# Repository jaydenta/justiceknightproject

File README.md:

# justiceknightproject
kicad and step files for new project

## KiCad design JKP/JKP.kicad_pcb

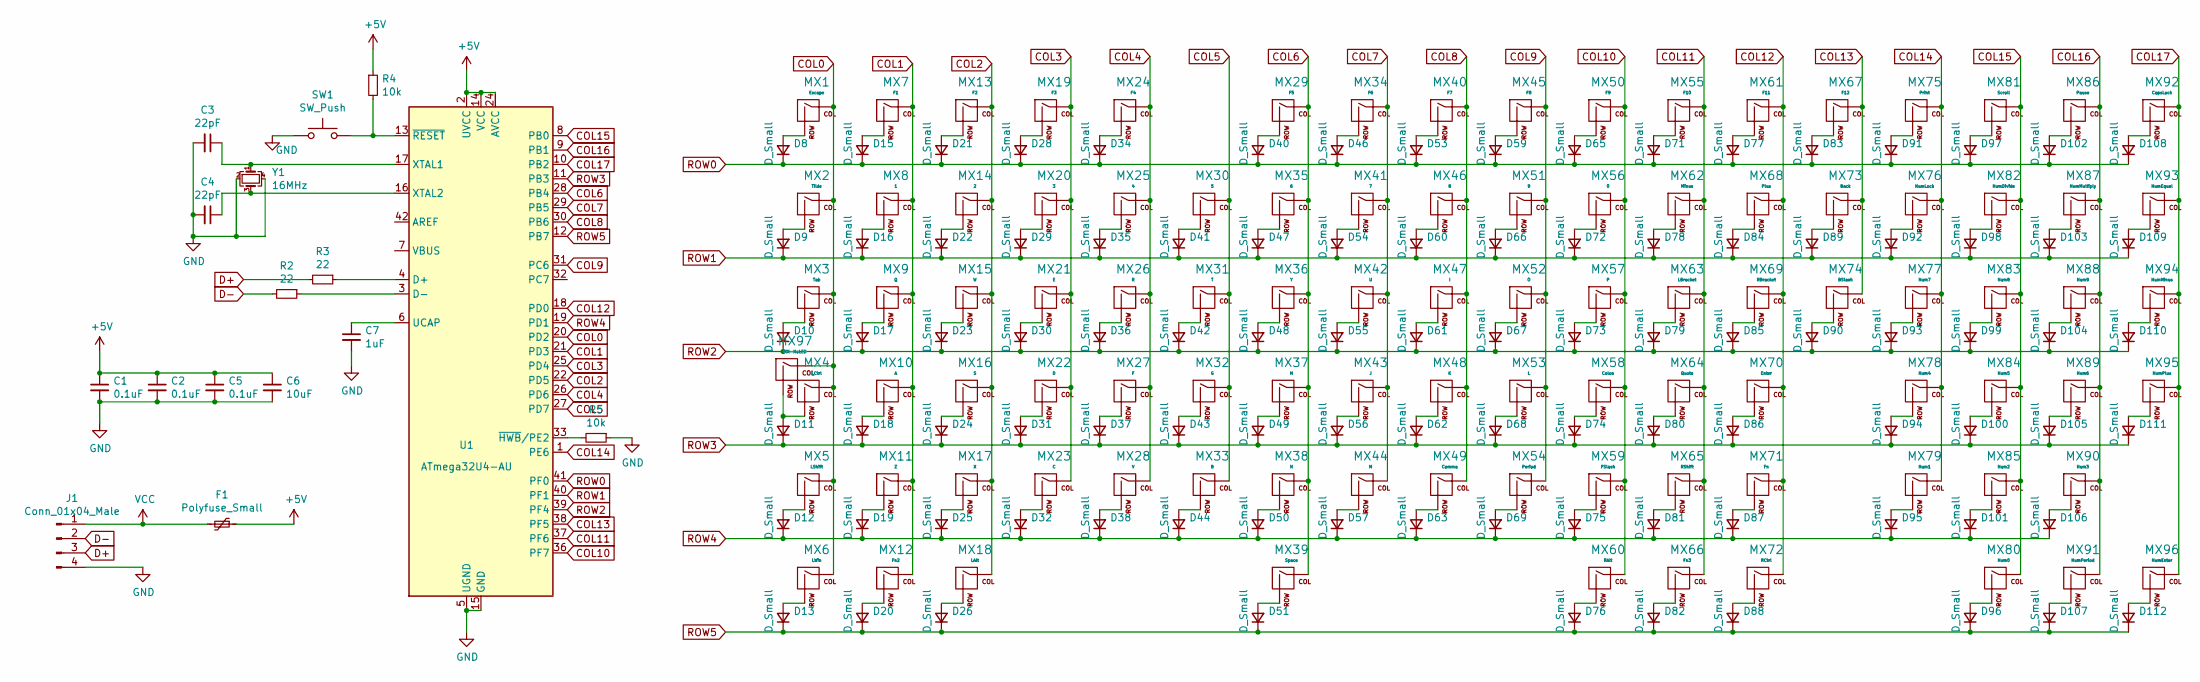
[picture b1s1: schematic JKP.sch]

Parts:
C1, C2, C5: 0.1uF; C_0805_2012Metric
C3, C4: 22pF; C_0805_2012Metric
C6: 10uF; C_0805_2012Metric
C7: 1uF; C_0805_2012Metric
D8, D9, D10, D11, D12, D13, D15, D16, D17, D18, D19, D20, D21, D22, D23, D24, D25, D26, D28, D29, D30, D31, D32, D34, D35, D36, D37, D38, D40, D41, D42, D43, D44, D46, D47, D48, D49, D50, D51, D53, D54, D55, D56, D57, D59, D60, D61, D62, D63, D65, D66, D67, D68, D69, D71, D72, D73, D74, D75, D76, D77, D78, D79, D80, D81, D82, D83, D84, D85, D86, D87, D88, D89, D90, D91, D92, D93, D94, D95, D96, D97, D98, D99, D100, D101, D102, D103, D104, D105, D106, D107, D108, D109, D110, D111, D112: D_Small; D_SOD-123
F1: Polyfuse_Small; Fuse_1206_3216Metric
J1: Conn_01x04_Male; JST_SH_SM04B-SRSS-TB_1x04-1MP_P1.00mm_Horizontal
MX1: Escape; MX-1U-NoLED
MX2: Tilde; MX-1U-NoLED
MX3: Tab; MX-1.5U-NoLED
MX4: LCtrl; MX-1.25U-NoLED
MX5: LShift; MX-2.25U-NoLED
MX6: LWin; MX-1.5U-NoLED
MX7: F1; MX-1U-NoLED
MX8: 1; MX-1U-NoLED
MX9: Q; MX-1U-NoLED
MX10: A; MX-1U-NoLED
MX11: Z; MX-1U-NoLED
MX12: Fn2; MX-1U-NoLED
MX13: F2; MX-1U-NoLED
MX14: 2; MX-1U-NoLED
MX15: W; MX-1U-NoLED
MX16: S; MX-1U-NoLED
MX17: X; MX-1U-NoLED
MX18: LAlt; MX-1.5U-NoLED
MX19: F3; MX-1U-NoLED
MX20: 3; MX-1U-NoLED
MX21: E; MX-1U-NoLED
MX22: D; MX-1U-NoLED
MX23: C; MX-1U-NoLED
MX24: F4; MX-1U-NoLED
MX25: 4; MX-1U-NoLED
MX26: R; MX-1U-NoLED
MX27: F; MX-1U-NoLED
MX28: V; MX-1U-NoLED
MX29: F5; MX-1U-NoLED
MX30: 5; MX-1U-NoLED
MX31: T; MX-1U-NoLED
MX32: G; MX-1U-NoLED
MX33: B; MX-1U-NoLED
MX34: F6; MX-1U-NoLED
MX35: 6; MX-1U-NoLED
MX36: Y; MX-1U-NoLED
MX37: H; MX-1U-NoLED
MX38: N; MX-1U-NoLED
MX39: Space; MX-7U-ReversedStabilizers-NoLED
MX40: F7; MX-1U-NoLED
MX41: 7; MX-1U-NoLED
MX42: U; MX-1U-NoLED
MX43: J; MX-1U-NoLED
MX44: M; MX-1U-NoLED
MX45: F8; MX-1U-NoLED
MX46: 8; MX-1U-NoLED
MX47: I; MX-1U-NoLED
MX48: K; MX-1U-NoLED
MX49: Comma; MX-1U-NoLED
MX50: F9; MX-1U-NoLED
MX51: 9; MX-1U-NoLED
MX52: O; MX-1U-NoLED
MX53: L; MX-1U-NoLED
MX54: Period; MX-1U-NoLED
MX55: F10; MX-1U-NoLED
MX56: 0; MX-1U-NoLED
MX57: P; MX-1U-NoLED
MX58: Colon; MX-1U-NoLED
MX59: FSlash; MX-1U-NoLED
MX60: RAlt; MX-1.5U-NoLED
MX61: F11; MX-1U-NoLED
MX62: Minus; MX-1U-NoLED
MX63: LBracket; MX-1U-NoLED
MX64: Quote; MX-1U-NoLED
MX65: RShift; MX-1.75U-NoLED
MX66: Fn3; MX-1U-NoLED
MX67: F12; MX-1U-NoLED
MX68: Plus; MX-1U-NoLED
MX69: RBracket; MX-1U-NoLED
MX70: Enter; MX-2.25U-NoLED
MX71: Fn; MX-1U-NoLED
MX72: RCtrl; MX-1.5U-NoLED
MX73: Back; MX-2U-NoLED
MX74: BSlash; MX-1.5U-NoLED
MX75: Print; MX-1U-NoLED
MX76: NumLock; MX-1U-NoLED
MX77: Num7; MX-1U-NoLED
MX78: Num4; MX-1U-NoLED
MX79: Num1; MX-1U-NoLED
MX80: Num0; MX-2U-ReversedStabilizers-NoLED
MX81: Scroll; MX-1U-NoLED
MX82: NumDivide; MX-1U-NoLED
MX83: Num8; MX-1U-NoLED
MX84: Num5; MX-1U-NoLED
MX85: Num2; MX-1U-NoLED
MX86: Pause; MX-1U-NoLED
MX87: NumMultiply; MX-1U-NoLED
MX88: Num9; MX-1U-NoLED
MX89: Num6; MX-1U-NoLED
MX90: Num3; MX-1U-NoLED
MX91: NumPeriod; MX-1U-NoLED
MX92: CapsLock; MX-1U-NoLED
MX93: NumEqual; MX-1U-NoLED
MX94: NumMinus; MX-1U-NoLED
MX95: NumPlus; MX-1U-NoLED
MX96: NumEnter; MX-2U-ReversedStabilizers-NoLED
MX97: MX-NoLED; MX-1.5U-NoLED
R2, R3: 22; R_0805_2012Metric
R4, R5: 10k; R_0805_2012Metric
SW1: SW_Push; SKQG-1155865
U1: ATmega32U4-AU; TQFP-44_10x10mm_P0.8mm
Y1: 16MHz; Crystal_SMD_3225-4Pin_3.2x2.5mm

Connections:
+5V: C1.1, C2.1, C5.1, C6.1, F1.1, R4.1, U1.2 (UVCC), U1.14 (VCC), U1.24 (AVCC), U1.34 (VCC), U1.44 (AVCC)
COL0: MX1.1 (COL), MX2.1 (COL), MX3.1 (COL), MX4.1 (COL), MX5.1 (COL), MX6.1 (COL), MX97.1 (COL), U1.20 (PD2)
COL1: MX7.1 (COL), MX8.1 (COL), MX9.1 (COL), MX10.1 (COL), MX11.1 (COL), MX12.1 (COL), U1.21 (PD3)
COL2: MX13.1 (COL), MX14.1 (COL), MX15.1 (COL), MX16.1 (COL), MX17.1 (COL), MX18.1 (COL), U1.22 (PD5)
COL3: MX19.1 (COL), MX20.1 (COL), MX21.1 (COL), MX22.1 (COL), MX23.1 (COL), U1.25 (PD4)
COL4: MX24.1 (COL), MX25.1 (COL), MX26.1 (COL), MX27.1 (COL), MX28.1 (COL), U1.26 (PD6)
COL5: MX30.1 (COL), MX31.1 (COL), MX32.1 (COL), MX33.1 (COL), U1.27 (PD7)
COL6: MX29.1 (COL), MX35.1 (COL), MX36.1 (COL), MX37.1 (COL), MX38.1 (COL), MX39.1 (COL), U1.28 (PB4)
COL7: MX34.1 (COL), MX41.1 (COL), MX42.1 (COL), MX43.1 (COL), MX44.1 (COL), U1.29 (PB5)
COL8: MX40.1 (COL), MX46.1 (COL), MX47.1 (COL), MX48.1 (COL), MX49.1 (COL), U1.30 (PB6)
COL9: MX45.1 (COL), MX51.1 (COL), MX52.1 (COL), MX53.1 (COL), MX54.1 (COL), U1.31 (PC6)
COL10: MX50.1 (COL), MX56.1 (COL), MX57.1 (COL), MX58.1 (COL), MX59.1 (COL), MX60.1 (COL), U1.36 (PF7)
COL11: MX55.1 (COL), MX62.1 (COL), MX63.1 (COL), MX64.1 (COL), MX65.1 (COL), MX66.1 (COL), U1.37 (PF6)
COL12: MX61.1 (COL), MX68.1 (COL), MX69.1 (COL), MX70.1 (COL), MX71.1 (COL), MX72.1 (COL), U1.18 (PD0)
COL13: MX67.1 (COL), MX73.1 (COL), MX74.1 (COL), U1.38 (PF5)
COL14: MX75.1 (COL), MX76.1 (COL), MX77.1 (COL), MX78.1 (COL), MX79.1 (COL), U1.1 (PE6)
COL15: MX80.1 (COL), MX81.1 (COL), MX82.1 (COL), MX83.1 (COL), MX84.1 (COL), MX85.1 (COL), U1.8 (PB0)
COL16: MX86.1 (COL), MX87.1 (COL), MX88.1 (COL), MX89.1 (COL), MX90.1 (COL), MX91.1 (COL), U1.9 (PB1)
COL17: MX92.1 (COL), MX93.1 (COL), MX94.1 (COL), MX95.1 (COL), MX96.1 (COL), U1.10 (PB2)
D+: J1.3, R3.2
D-: J1.2, R2.2
GND: C1.2, C2.2, C3.2, C4.2, C5.2, C6.2, C7.2, J1.4, R5.1, SW1.1, U1.5 (UGND), U1.15 (GND), U1.23 (GND), U1.35 (GND), U1.43 (GND), Y1.2, Y1.4
unnamed: C3.1, U1.17 (XTAL1), Y1.1
unnamed: C4.1, U1.16 (XTAL2), Y1.3
unnamed: C7.1, U1.6 (UCAP)
unnamed: D8.2 (A), MX1.2 (ROW)
unnamed: D9.2 (A), MX2.2 (ROW)
unnamed: D10.2 (A), MX3.2 (ROW)
unnamed: D11.2 (A), MX4.2 (ROW), MX97.2 (ROW)
unnamed: D12.2 (A), MX5.2 (ROW)
unnamed: D13.2 (A), MX6.2 (ROW)
unnamed: D15.2 (A), MX7.2 (ROW)
unnamed: D16.2 (A), MX8.2 (ROW)
unnamed: D17.2 (A), MX9.2 (ROW)
unnamed: D18.2 (A), MX10.2 (ROW)
unnamed: D19.2 (A), MX11.2 (ROW)
unnamed: D20.2 (A), MX12.2 (ROW)
unnamed: D21.2 (A), MX13.2 (ROW)
unnamed: D22.2 (A), MX14.2 (ROW)
unnamed: D23.2 (A), MX15.2 (ROW)
unnamed: D24.2 (A), MX16.2 (ROW)
unnamed: D25.2 (A), MX17.2 (ROW)
unnamed: D26.2 (A), MX18.2 (ROW)
unnamed: D28.2 (A), MX19.2 (ROW)
unnamed: D29.2 (A), MX20.2 (ROW)
unnamed: D30.2 (A), MX21.2 (ROW)
unnamed: D31.2 (A), MX22.2 (ROW)
unnamed: D32.2 (A), MX23.2 (ROW)
unnamed: D34.2 (A), MX24.2 (ROW)
unnamed: D35.2 (A), MX25.2 (ROW)
unnamed: D36.2 (A), MX26.2 (ROW)
unnamed: D37.2 (A), MX27.2 (ROW)
unnamed: D38.2 (A), MX28.2 (ROW)
unnamed: D40.2 (A), MX29.2 (ROW)
unnamed: D41.2 (A), MX30.2 (ROW)
unnamed: D42.2 (A), MX31.2 (ROW)
unnamed: D43.2 (A), MX32.2 (ROW)
unnamed: D44.2 (A), MX33.2 (ROW)
unnamed: D46.2 (A), MX34.2 (ROW)
unnamed: D47.2 (A), MX35.2 (ROW)
unnamed: D48.2 (A), MX36.2 (ROW)
unnamed: D49.2 (A), MX37.2 (ROW)
unnamed: D50.2 (A), MX38.2 (ROW)
unnamed: D51.2 (A), MX39.2 (ROW)
unnamed: D53.2 (A), MX40.2 (ROW)
unnamed: D54.2 (A), MX41.2 (ROW)
unnamed: D55.2 (A), MX42.2 (ROW)
unnamed: D56.2 (A), MX43.2 (ROW)
unnamed: D57.2 (A), MX44.2 (ROW)
unnamed: D59.2 (A), MX45.2 (ROW)
unnamed: D60.2 (A), MX46.2 (ROW)
unnamed: D61.2 (A), MX47.2 (ROW)
unnamed: D62.2 (A), MX48.2 (ROW)
unnamed: D63.2 (A), MX49.2 (ROW)
unnamed: D65.2 (A), MX50.2 (ROW)
unnamed: D66.2 (A), MX51.2 (ROW)
unnamed: D67.2 (A), MX52.2 (ROW)
unnamed: D68.2 (A), MX53.2 (ROW)
unnamed: D69.2 (A), MX54.2 (ROW)
unnamed: D71.2 (A), MX55.2 (ROW)
unnamed: D72.2 (A), MX56.2 (ROW)
unnamed: D73.2 (A), MX57.2 (ROW)
unnamed: D74.2 (A), MX58.2 (ROW)
unnamed: D75.2 (A), MX59.2 (ROW)
unnamed: D76.2 (A), MX60.2 (ROW)
unnamed: D77.2 (A), MX61.2 (ROW)
unnamed: D78.2 (A), MX62.2 (ROW)
unnamed: D79.2 (A), MX63.2 (ROW)
unnamed: D80.2 (A), MX64.2 (ROW)
unnamed: D81.2 (A), MX65.2 (ROW)
unnamed: D82.2 (A), MX66.2 (ROW)
unnamed: D83.2 (A), MX67.2 (ROW)
unnamed: D84.2 (A), MX68.2 (ROW)
unnamed: D85.2 (A), MX69.2 (ROW)
unnamed: D86.2 (A), MX70.2 (ROW)
unnamed: D87.2 (A), MX71.2 (ROW)
unnamed: D88.2 (A), MX72.2 (ROW)
unnamed: D89.2 (A), MX73.2 (ROW)
unnamed: D90.2 (A), MX74.2 (ROW)
unnamed: D91.2 (A), MX75.2 (ROW)
unnamed: D92.2 (A), MX76.2 (ROW)
unnamed: D93.2 (A), MX77.2 (ROW)
unnamed: D94.2 (A), MX78.2 (ROW)
unnamed: D95.2 (A), MX79.2 (ROW)
unnamed: D96.2 (A), MX80.2 (ROW)
unnamed: D97.2 (A), MX81.2 (ROW)
unnamed: D98.2 (A), MX82.2 (ROW)
unnamed: D99.2 (A), MX83.2 (ROW)
unnamed: D100.2 (A), MX84.2 (ROW)
unnamed: D101.2 (A), MX85.2 (ROW)
unnamed: D102.2 (A), MX86.2 (ROW)
unnamed: D103.2 (A), MX87.2 (ROW)
unnamed: D104.2 (A), MX88.2 (ROW)
unnamed: D105.2 (A), MX89.2 (ROW)
unnamed: D106.2 (A), MX90.2 (ROW)
unnamed: D107.2 (A), MX91.2 (ROW)
unnamed: D108.2 (A), MX92.2 (ROW)
unnamed: D109.2 (A), MX93.2 (ROW)
unnamed: D110.2 (A), MX94.2 (ROW)
unnamed: D111.2 (A), MX95.2 (ROW)
unnamed: D112.2 (A), MX96.2 (ROW)
unnamed: R2.1, U1.3 (D-)
unnamed: R3.1, U1.4 (D+)
unnamed: R4.2, SW1.2, U1.13 (~RESET)
unnamed: R5.2, U1.33 (~HWB~/PE2)
ROW0: D8.1 (K), D15.1 (K), D21.1 (K), D28.1 (K), D34.1 (K), D40.1 (K), D46.1 (K), D53.1 (K), D59.1 (K), D65.1 (K), D71.1 (K), D77.1 (K), D83.1 (K), D91.1 (K), D97.1 (K), D102.1 (K), D108.1 (K), U1.41 (PF0)
ROW1: D9.1 (K), D16.1 (K), D22.1 (K), D29.1 (K), D35.1 (K), D41.1 (K), D47.1 (K), D54.1 (K), D60.1 (K), D66.1 (K), D72.1 (K), D78.1 (K), D84.1 (K), D89.1 (K), D92.1 (K), D98.1 (K), D103.1 (K), D109.1 (K), U1.40 (PF1)
ROW2: D10.1 (K), D17.1 (K), D23.1 (K), D30.1 (K), D36.1 (K), D42.1 (K), D48.1 (K), D55.1 (K), D61.1 (K), D67.1 (K), D73.1 (K), D79.1 (K), D85.1 (K), D90.1 (K), D93.1 (K), D99.1 (K), D104.1 (K), D110.1 (K), U1.39 (PF4)
ROW3: D11.1 (K), D18.1 (K), D24.1 (K), D31.1 (K), D37.1 (K), D43.1 (K), D49.1 (K), D56.1 (K), D62.1 (K), D68.1 (K), D74.1 (K), D80.1 (K), D86.1 (K), D94.1 (K), D100.1 (K), D105.1 (K), D111.1 (K), U1.11 (PB3)
ROW4: D12.1 (K), D19.1 (K), D25.1 (K), D32.1 (K), D38.1 (K), D44.1 (K), D50.1 (K), D57.1 (K), D63.1 (K), D69.1 (K), D75.1 (K), D81.1 (K), D87.1 (K), D95.1 (K), D101.1 (K), D106.1 (K), U1.19 (PD1)
ROW5: D13.1 (K), D20.1 (K), D26.1 (K), D51.1 (K), D76.1 (K), D82.1 (K), D88.1 (K), D96.1 (K), D107.1 (K), D112.1 (K), U1.12 (PB7)
VCC: F1.2, J1.1

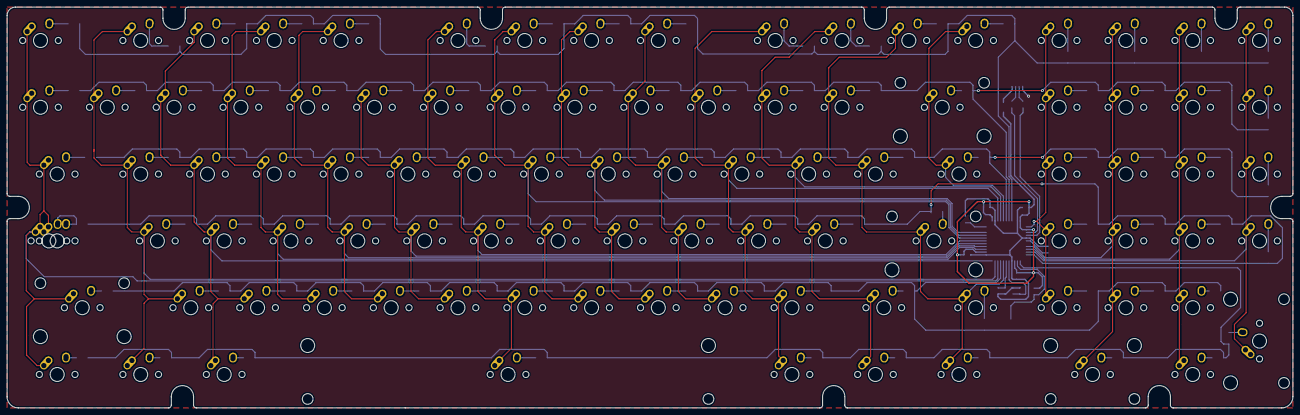
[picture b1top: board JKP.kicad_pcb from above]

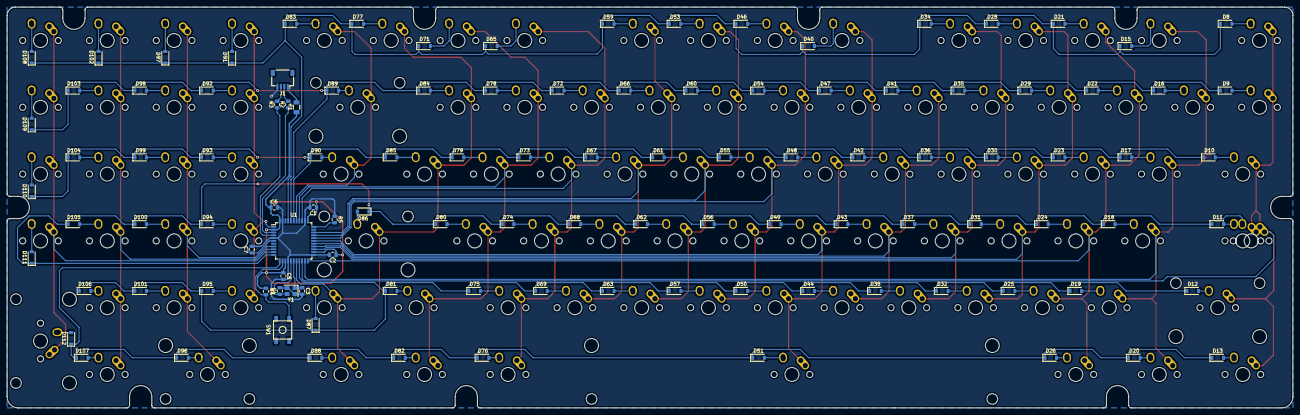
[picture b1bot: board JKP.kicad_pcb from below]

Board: 2 copper layers, 366.7 x 114.3 mm, 209 parts (112 on the bottom side), 132 nets.

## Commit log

2021-12-05 pcb files
2021-12-06 finished kicad schematic
2021-12-06 physical pcb components placement 40% done
2021-12-07 routing pcb part 1
2021-12-07 Finished PCB v1 No LED
2021-12-12 double checking
2021-12-12 changed PCB to screwless design
2021-12-15 screwless pcb cutouts
2021-12-17 final PCB v1
2021-12-20 finised 3d files
2021-12-22 misc stuff
2022-01-01 fixed VBUS not connected
